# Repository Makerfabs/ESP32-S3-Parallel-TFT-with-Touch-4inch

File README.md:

# Makerfabs ESP32-S3 Parallel TFT with Touch 4inch

```c++
/*
Version:        V1.1
Author:            Vincent
Create Date:    2023/2/4
Note:
        V1.2：Now support LovyanGFX！
        V1.1: Add example and update readme.
*/
```

[TOC]

# Makerfabs

[Makerfabs home page](https://www.makerfabs.com/)

[Makerfabs Wiki](https://wiki.makerfabs.com/)

# Makerfabs ESP32-S3 Parallel TFT with Touch 4inch

## Intruduce

Product Link ：[ESP32-S3 Parallel TFT with Touch 4.0" 480*480 ST7701](https://www.makerfabs.com/esp32-s3-parallel-tft-with-touch-4-inch.html)

Wiki Link : [ESP32-S3 Parallel 4.0" TFT with Touch](https://wiki.makerfabs.com/ESP32_S3_Parallel_4.0_TFT_with_Touch.html)

The Latest ESP32-S3 4.0 inch display with 480*480 resolution, it integrated display/ touch/ audio speaker/ Lipo charger, to make this product ideal for applications such as IoT controlling, electronic photo frame, etc.

## Feature

- 4 inch RGB IPS display, it communicates with the controller ESP32S3 with 3SPI+RGB5/6/5 interface, with FPS >80;
- 5 points Touch;
- Onboard 16G SD card for storage;
- Lipo battery socket and charger, support any 3.7v lipo battery;
- On board speaker connector. This product is shipped with a 3 ohm 4w, 3528 speaker, the voice loud and clean, suitable for most applications;
- 2x Onboard Mabee connectors, support multiple Mabee/ Grove modules;

# Code

## Complier Option

- Install board : ESP32 .
- Install libraries：

[ESP32-audioI2S]([GitHub - schreibfaul1/ESP32-audioI2S: Play mp3 files from SD via I2S](https://github.com/schreibfaul1/ESP32-audioI2S))

- Use type-c use cable connect USB-TTL to PC.
- Select "ESP32-S3 DEV Module"
- Select PSRAM "OPI PSRAM"

"mf_Lvgl" library is modified from Lvgl library (version 8.3.2). 

Please unzip "lib/mf_Lvgl.zip" and copy to arduino library directory.

## Factory test program

\example\esp32s3_4.0_tft_fw_test

You can run this file test if you feel that your hardware is not working properly. 

In addition, it is necessary to decompress the compressed package in the sd_file folder and copy all the pictures and music in it to the TF card.

## Attention

Our Arduino_GFX_library version is 1.3.1, while the latest version is 1.3.4. The two versions are incompatible the running code. Our customer@Tim successfully ran the Arduino_gfx_Library version after modifying the configuration in the code on version 1.3.4.

```
Arduino_DataBus *bus = new Arduino_SWSPI(
    GFX_NOT_DEFINED /* DC */, 1 /* CS */,
    12 /* SCK */, 11 /* MOSI */, GFX_NOT_DEFINED /* MISO */);

Arduino_ESP32RGBPanel *rgbpanel = new Arduino_ESP32RGBPanel(
    45 /* DE */, 4 /* VSYNC */, 5 /* HSYNC */, 21 /* PCLK */,
    39 /* R0 */, 40 /* R1 */, 41 /* R2 */, 42 /* R3 */, 2 /* R4 */,
    0 /* G0 */, 9 /* G1 */, 14 /* G2 */, 47 /* G3 */, 48 /* G4 */, 3 /* G5 */,
    6 /* B0 */, 7 /* B1 */, 15 /* B2 */, 16 /* B3 */, 8 /* B4 */,
    1 /* hsync_polarity */, 10 /* hsync_front_porch */, 8 /* hsync_pulse_width */, 50 /* hsync_back_porch */,
    1 /* vsync_polarity */, 10 /* vsync_front_porch */, 8 /* vsync_pulse_width */, 20 /* vsync_back_porch */);

Arduino_RGB_Display *gfx = new Arduino_RGB_Display(
    480 /* width */, 480 /* height */, rgbpanel, 0 /* rotation */, true /* auto_flush */,
    bus, GFX_NOT_DEFINED /* RST */, st7701_type1_init_operations, sizeof(st7701_type1_init_operations));
```

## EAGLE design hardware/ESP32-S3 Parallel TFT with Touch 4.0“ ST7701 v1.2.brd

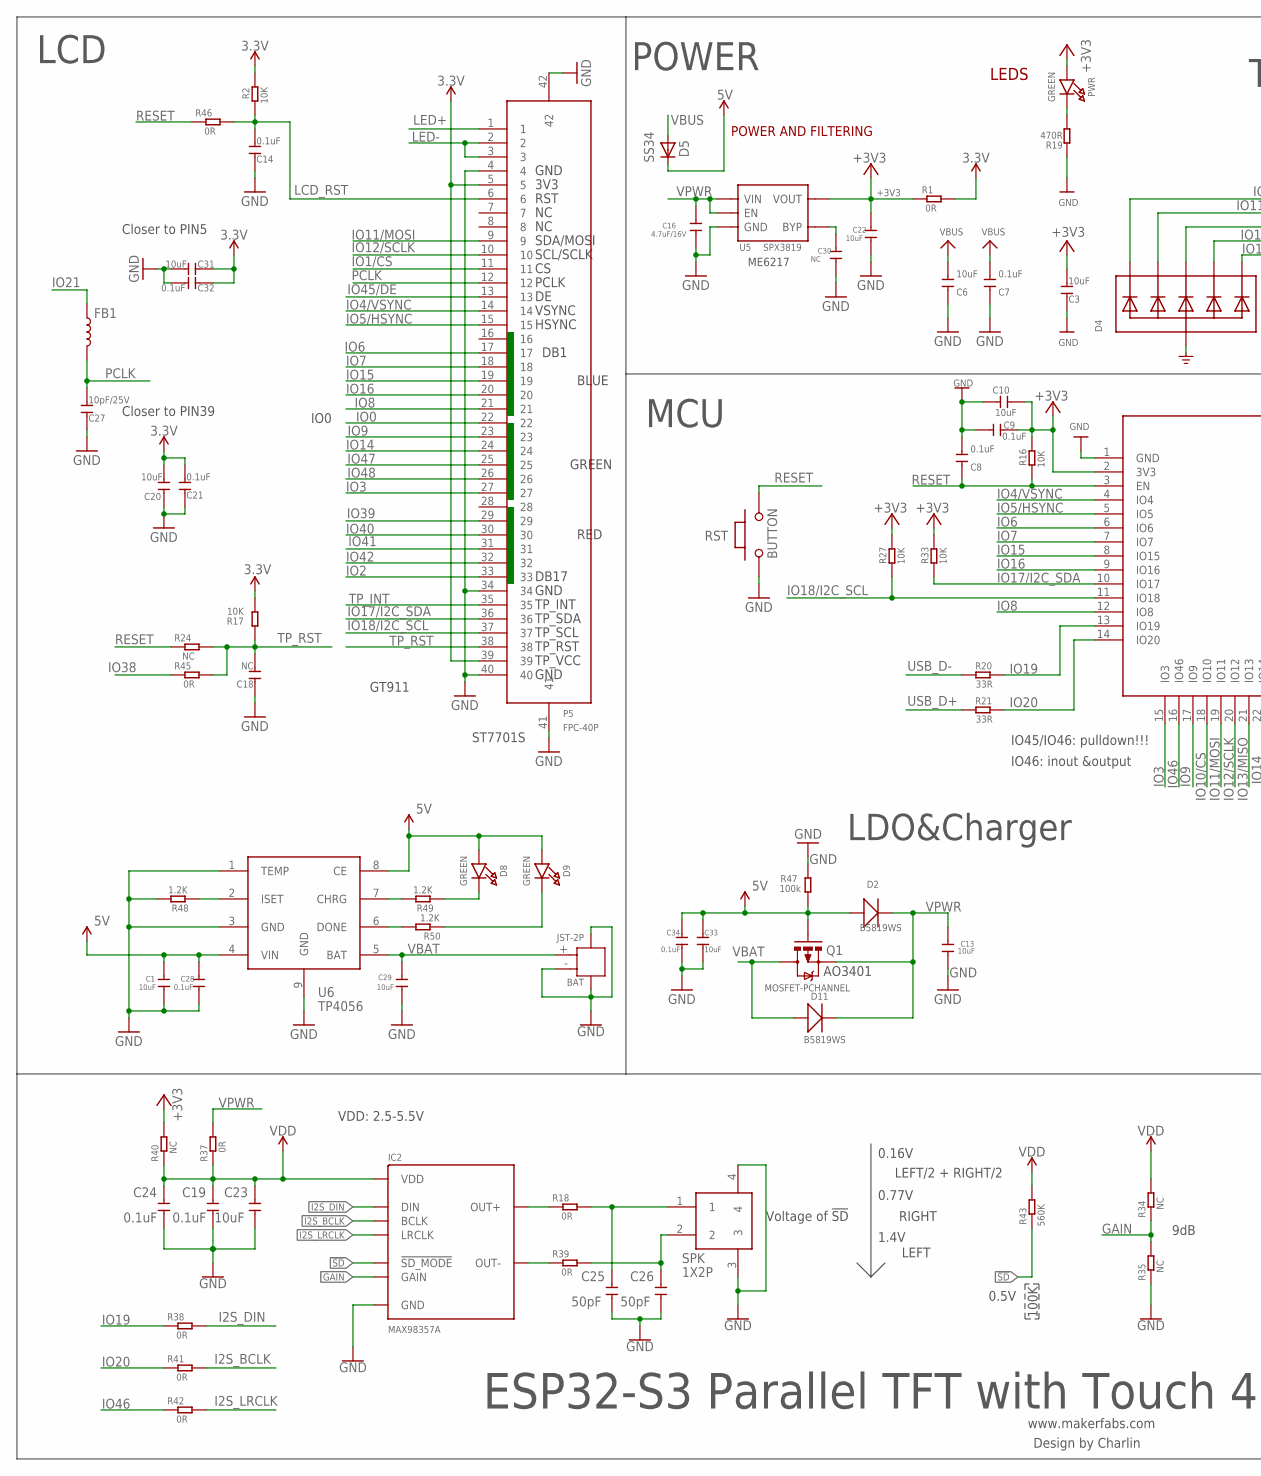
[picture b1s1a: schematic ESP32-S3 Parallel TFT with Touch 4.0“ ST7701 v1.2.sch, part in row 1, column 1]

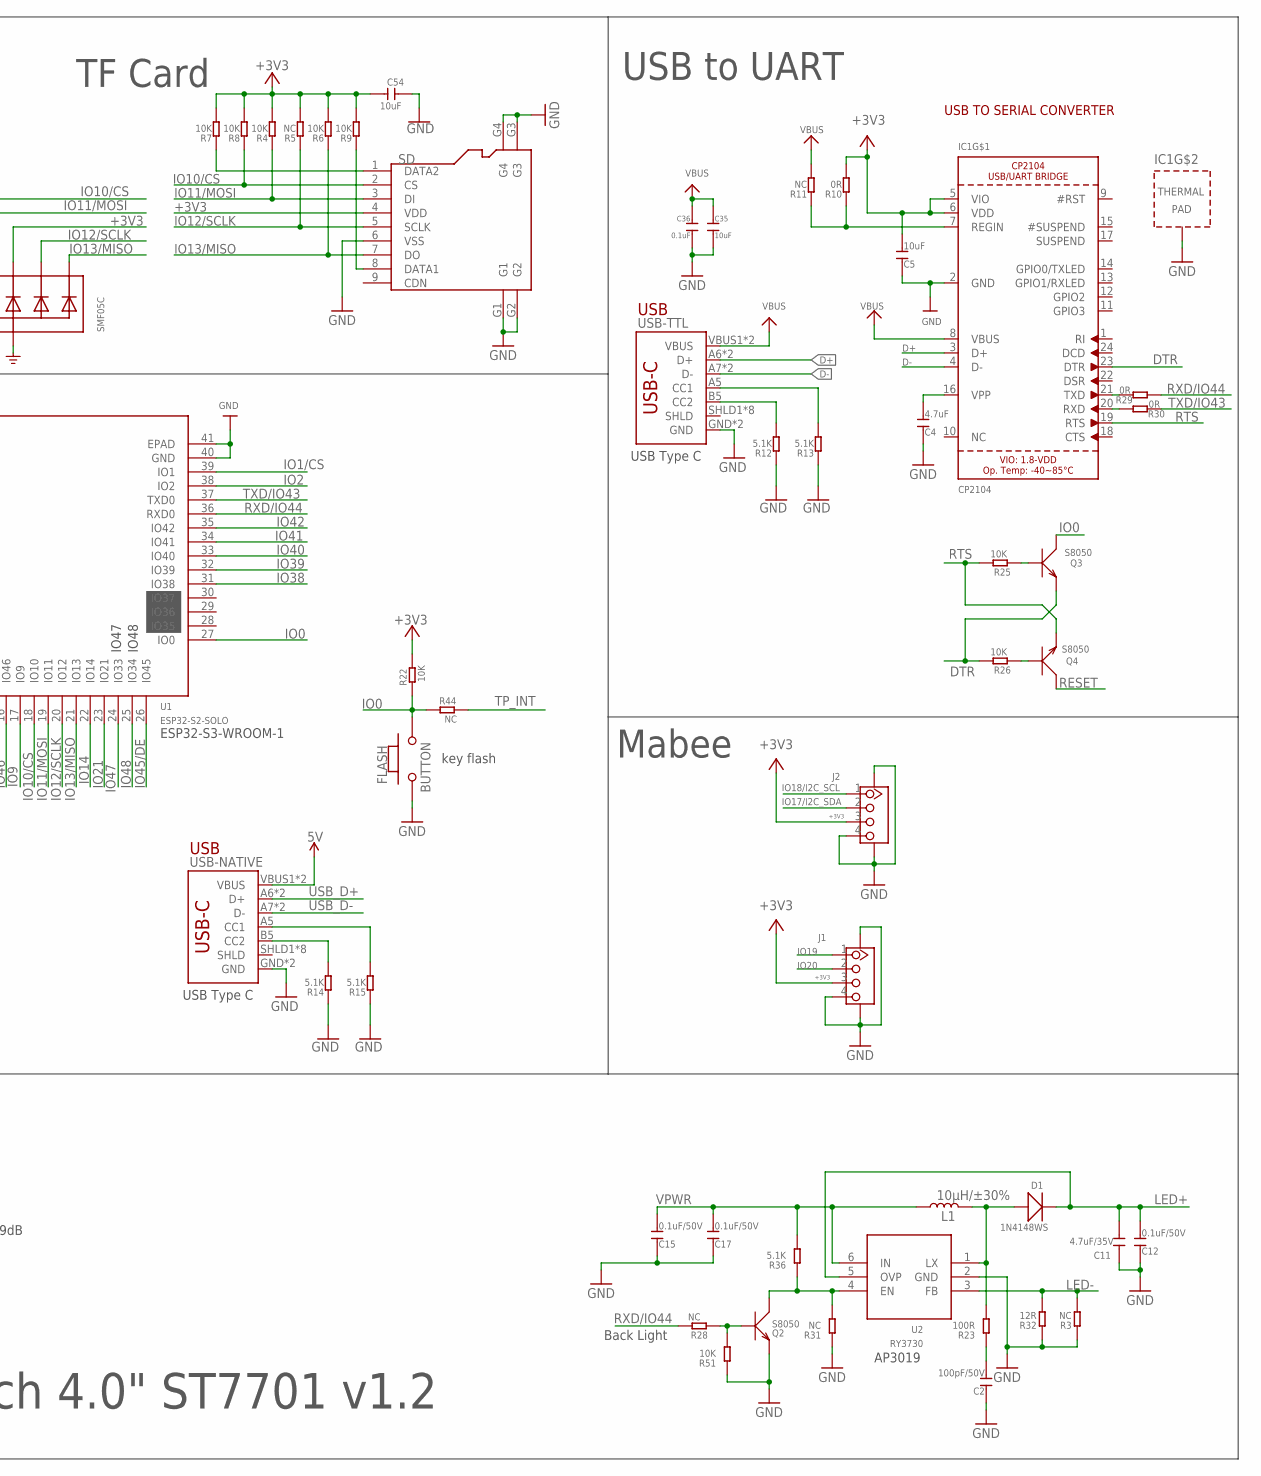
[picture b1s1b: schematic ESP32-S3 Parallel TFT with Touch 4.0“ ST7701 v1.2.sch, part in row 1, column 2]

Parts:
BAT: JST-2P; HW2-SMD-2.0-90D
C1, C13, C22, C23, C29, C33, C35: 10uF; 0603
C2: 100pF/50V; DISCRETE_C0603
C3, C5, C6, C10, C20, C31, C54: 10uF; DISCRETE_C0603
C4: 4.7uF; DISCRETE_C0603
C7, C8, C9, C14, C21, C32: 0.1uF; DISCRETE_C0603
C11: 4.7uF/35V; DISCRETE_C1206
C12, C15, C17: 0.1uF/50V; DISCRETE_C0603
C16: 4.7uF/16V; 0603
C18: NC; DISCRETE_C0603
C19, C24, C28, C34, C36: 0.1uF; 0603
C25, C26: 50pF; 0603
C27: 10pF/25V; DISCRETE_C0603
C30: NC; 0603
D1: 1N4148WS; SOD323
D2, D11: B5819WS; SOD323
D4: SMF05C; SOT363
D5: SS34; DO-214AC
D8, D9: GREEN; CHIPLED_0805_NOOUTLINE
FB1: INDUCTORFB-30OHM; 0603
FLASH: BUTTON; 157SW
IC1: CP2104; QFN24_4MM_SMSC
IC2: MAX98357A; TQFN-16
J1, J2: GROVE-CONNECTOR-SMD'90D'; HW4-SMD-2.0-90D
L1: 10µH/±30%; CR54
P5: FPC-40P; SMD42-50P-2560L490W
PWR: GREEN; CHIPLED_0805_NOOUTLINE
Q1: MOSFET-PCHANNEL; SOT23-3
Q2, Q3, Q4: S8050; SOT23
R1, R18, R29, R30, R37, R38, R39, R41, R42, R45, R46: 0R; R0603
R2, R16, R22, R25, R26, R27, R33: 10K; R0603
R3, R5, R11, R28, R31: NC; DISCRETE_R0603
R4, R6, R7, R8, R9, R17, R51: 10K; DISCRETE_R0603
R10: 0R; DISCRETE_R0603
R12, R13, R14, R15, R36: 5.1K; DISCRETE_R0603
R19: 470R; DISCRETE_R0603
R20, R21: 33R; R0603
R23: 100R; DISCRETE_R0603
R24, R34, R35, R40, R44: NC; R0603
R32: 12R; DISCRETE_R0603
R43: 560K; R0603
R47: 100k; R0603
R48, R49, R50: 1.2K; R0603
RST: BUTTON; 157SW
SD: HOLDER-MICROSD-9P; 9P-SMD-W/-RING
SPK: 1X2P; 1X2P-SMT1.25MM
U1: ESP32­S2­SOLO; ESP32-­S2-­SOLO
U2: RY3730; SOT23-6
U5: SPX3819; SOT23-5
U6: TP4056; SOP8-1.27P
USB-NATIVE: USB_C5; USB-C-16P-5
USB-TTL: USB_C5; USB-C-16P-5

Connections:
3.3V: C20.2, C21.2, C31.1, C32.1, P5.5, P5.39, R1.2, R2.2, R17.2
5V: C1.1, C28.1, C33.2, C34.1, D2.+, D5.C, D8.A, D9.A, Q1.1 (G), R47.1, U6.4 (VIN), U6.8 (CE), USB-NATIVE.VBUS1 (VBUS), USB-NATIVE.VBUS2 (VBUS)
!SD: IC2.P$4 (!SD_MODE), R43.1
+3V3: C3.2, C5.2, C9.1, C10.1, C22.1, C54.2, D4.4 (C3), IC1.5 (VIO), IC1.6 (VDD), J1.3, J2.3, PWR.A, R1.1, R4.2, R5.2, R6.2, R7.2, R8.2, R9.2, R10.2, R16.2, R22.2, R27.2, R33.2, R40.2, SD.4 (VDD), U1.2 (3V3), U5.5 (VOUT)
D+: IC1.3 (D+), USB-TTL.A6 (D+), USB-TTL.B6 (D+)
D-: IC1.4 (D-), USB-TTL.A7 (D-), USB-TTL.B7 (D-)
DTR: IC1.23 (DTR), Q3.2 (E), R26.2
GAIN: IC2.P$2 (GAIN), R34.1, R35.2
GND: BAT.3, BAT.4, BAT.- (2), C1.2, C2.1, C3.1, C4.1, C5.1, C6.1, C7.1, C8.2, C9.2, C10.2, C11.1, C12.1, C13.1, C14.1, C15.1, C16.2, C17.1, C18.1, C19.1, C20.1, C21.1, C22.2, C23.1, C24.1, C25.1, C26.1, C27.1, C28.2, C29.2, C30.2, C31.2, C32.2, C33.1, C34.2, C35.1, C36.2, C54.1, D4.2 (A), FLASH.1, IC1.2 (GND), IC1.THERM (TP), IC2.P$3 (GND), IC2.P$11 (GND), IC2.P$15 (GND), IC2.P$EP (GND), J1.4, J1.SS1, J1.SS2, J2.4, J2.SS1, J2.SS2, P5.4, P5.34, P5.40, P5.41, P5.42, Q2.2 (E), R3.1, R12.1, R13.1, R14.1, R15.1, R19.1, R31.1, R32.1, R35.1, R47.2, R48.2, R51.1, RST.1, SD.6 (VSS), SD.G1, SD.G2, SD.G3, SD.G4, SPK.3, SPK.4, U1.1 (GND), U1.40 (GND), U1.41 (EPAD), U2.2 (GND), U5.2 (GND), U6.1 (TEMP), U6.3 (GND), U6.9 (GND), USB-NATIVE.GND, USB-NATIVE.GND2 (GND), USB-TTL.GND, USB-TTL.GND2 (GND)
I2S_BCLK: IC2.P$16 (BCLK), R41.2
I2S_DIN: IC2.P$1 (DIN), R38.2
I2S_LRCLK: IC2.P$14 (LRCLK), R42.2
IO0: FLASH.2, P5.22, Q3.3 (C), R22.1, R44.1, U1.27 (IO0)
IO1/CS: P5.11, U1.39 (IO1)
IO2: P5.33, U1.38 (IO2)
IO3: P5.27, U1.15 (IO3)
IO4/VSYNC: P5.14, U1.4 (IO4)
IO5/HSYNC: P5.15, U1.5 (IO5)
IO6: P5.17, U1.6 (IO6)
IO7: P5.18, U1.7 (IO7)
IO8: P5.21, U1.12 (IO8)
IO9: P5.23, U1.17 (IO9)
IO10/CS: D4.1 (C1), R8.1, SD.2 (CS), U1.18 (IO10)
IO11/MOSI: D4.3 (C2), P5.9, R4.1, SD.3 (DI), U1.19 (IO11)
IO12/SCLK: D4.5 (C4), P5.10, R5.1, SD.5 (SCLK), U1.20 (IO12)
IO13/MISO: D4.6 (C5), R6.1, SD.7 (DO), U1.21 (IO13)
IO14: P5.24, U1.22 (IO14)
IO15: P5.19, U1.8 (IO15)
IO16: P5.20, U1.9 (IO16)
IO17/I2C_SDA: J2.2, P5.36, R33.1, U1.10 (IO17)
IO18/I2C_SCL: J2.1, P5.37, R27.1, U1.11 (IO18)
IO19: J1.1, R20.2, R38.1, U1.13 (IO19)
IO20: J1.2, R21.2, R41.1, U1.14 (IO20)
IO21: FB1.1, U1.23 (IO21)
IO38: R45.1, U1.31 (IO38)
IO39: P5.29, U1.32 (IO39)
IO40: P5.30, U1.33 (IO40)
IO41: P5.31, U1.34 (IO41)
IO42: P5.32, U1.35 (IO42)
IO45/DE: P5.13, U1.26 (IO45)
IO46: R42.1, U1.16 (IO46)
IO47: P5.25, U1.24 (IO33)
IO48: P5.26, U1.25 (IO34)
LCD_RST: C14.2, P5.6, R2.1, R46.2
LED+: C11.2, C12.2, D1.-, P5.1, U2.5 (OVP)
LED-: P5.2, P5.3, R3.2, R32.2, U2.3 (FB)
unnamed: C4.2, IC1.16 (VPP)
unnamed: Q4.1 (B), R26.1
unnamed: Q3.1 (B), R25.1
unnamed: IC2.P$9 (OUT+), R18.1
unnamed: R15.2, USB-NATIVE.A5 (CC1)
unnamed: PWR.C, R19.2
unnamed: Q2.1 (B), R28.1, R51.2
unnamed: R13.2, USB-TTL.A5 (CC1)
unnamed: R12.2, USB-TTL.B5 (CC2)
unnamed: IC1.7 (REGIN), R10.1, R11.1
unnamed: IC2.P$10 (OUT-), R39.1
unnamed: R14.2, USB-NATIVE.B5 (CC2)
unnamed: C25.2, R18.2, SPK.1
unnamed: C26.2, R39.2, SPK.2
unnamed: D1.+, L1.P$2 (2), R23.2, U2.1 (LX)
unnamed: IC1.21 (TXD), R29.2
unnamed: IC1.20 (RXD), R30.2
unnamed: C2.2, R23.1
unnamed: R48.1, U6.2 (ISET)
unnamed: Q2.3 (C), R31.2, R36.1, U2.4 (EN)
unnamed: R49.2, U6.7 (CHRG)
unnamed: R50.2, U6.6 (DONE)
unnamed: D8.C, R49.1
unnamed: D9.C, R50.1
unnamed: R7.1, SD.1 (DATA2)
unnamed: R9.1, SD.8 (DATA1)
unnamed: C30.1, U5.4 (BYP)
PCLK: C27.2, FB1.2, P5.12
RESET: C8.1, Q4.3 (C), R16.1, R24.1, R46.1, RST.2, U1.3 (EN)
RTS: IC1.19 (RTS), Q4.2 (E), R25.2
RXD/IO44: R28.2, R29.1, U1.36 (RXD0)
TP_INT: P5.35, R44.2
TP_RST: C18.2, P5.38, R17.1, R24.2, R45.2
TXD/IO43: R30.1, U1.37 (TXD0)
USB_D+: R21.1, USB-NATIVE.A6 (D+), USB-NATIVE.B6 (D+)
USB_D-: R20.1, USB-NATIVE.A7 (D-), USB-NATIVE.B7 (D-)
VBAT: BAT.+ (1), C29.1, D11.+, Q1.3 (D), U6.5 (BAT)
VBUS: C6.2, C7.2, C35.2, C36.1, D5.A, IC1.8 (VBUS), R11.2, USB-TTL.VBUS1 (VBUS), USB-TTL.VBUS2 (VBUS)
VDD: C19.2, C23.2, C24.2, IC2.P$7 (VDD), IC2.P$8 (VDD), R34.2, R37.1, R40.1, R43.2
VPWR: C13.2, C15.2, C16.1, C17.2, D2.-, D11.-, L1.P$1 (1), Q1.2 (S), R36.2, R37.2, U2.6 (IN), U5.1 (VIN), U5.3 (EN)

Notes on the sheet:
www.makerfabs.com
Design by Charlin
USB
LEDS
POWER AND FILTERING
USB TO SERIAL CONVERTER
key flash
ESP32-S3 Parallel TFT with Touch 4.0" ST7701 v1.2
POWER
USB to UART
USB Type C
TF Card
GT911
Back Light
IO45/IO46: pulldown!!!
IO46: inout &output
Mabee
LCD
MCU
ESP32-S3-WROOM-1
IO47
IO48
Closer to PIN5
3V3
DB1
RST
TP_INT
SDA/MOSI
SCL/SCLK
PCLK
VSYNC
HSYNC
TP_SDA
TP_SCL
TP_RST
TP_VCC
ST7701S
GND
DB17
BLUE

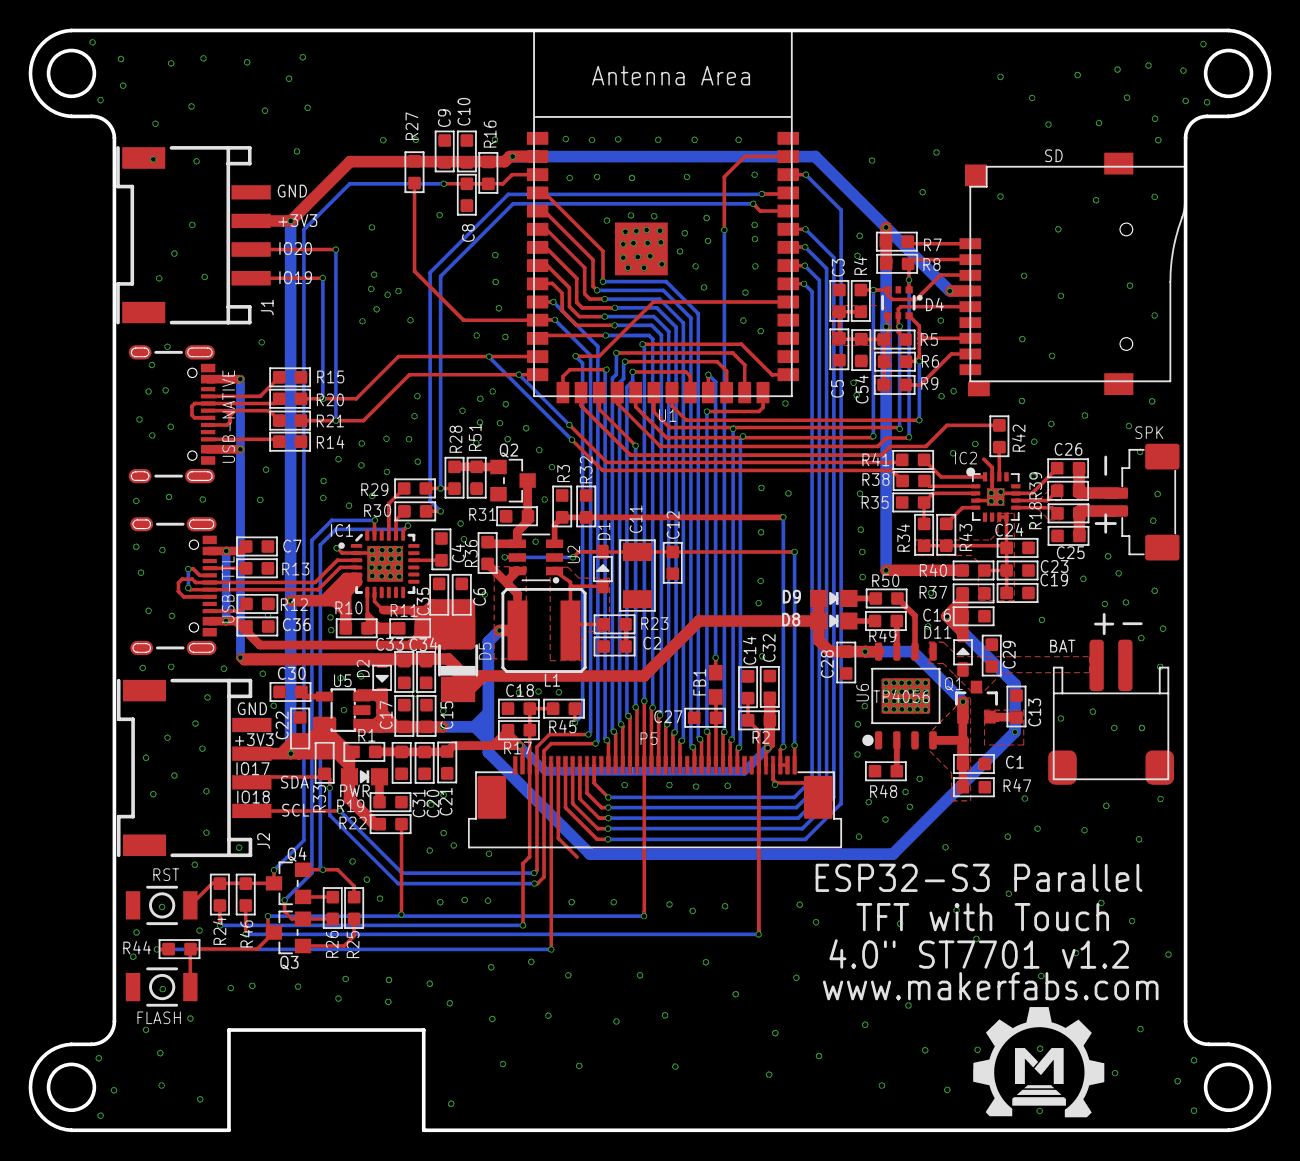
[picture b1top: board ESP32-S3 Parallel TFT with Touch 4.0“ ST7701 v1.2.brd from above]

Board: 2 copper layers, 86.5 x 76.8 mm, 119 parts (0 on the bottom side), 86 nets.

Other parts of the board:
U$1: MAKERFABS_0.3

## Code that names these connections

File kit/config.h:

#ifndef MF_CONFIG_H
#define MF_CONFIG_H

#include <SPI.h>
#include <FS.h>
#include <Wire.h>
#include <SD.h>
#include <Audio.h>
#include <Arduino_GFX_Library.h>
#include <TAMC_GT911.h>
#include <ArduinoJson.h>
#include <HTTPClient.h>
#include <Adafruit_MLX90640.h>
#include <Adafruit_SGP30.h>
#include <Adafruit_SHT31.h>
#include <ESPAsyncWebServer.h>

#include "JpegFunc.h"

// SD
#define SD_SCK 12
#define SD_MISO 13
#define SD_MOSI 11
#define SD_CS 10

// I2S
#define I2S_DOUT 19
#define I2S_BCLK 20
#define I2S_LRCK 46

// Touch
#define I2C_SDA_PIN 17
#define I2C_SCL_PIN 18
#define TOUCH_INT -1
#define TOUCH_RST 38

#define TOUCH_ROTATION ROTATION_NORMAL
#define TOUCH_MAP_X1 480
#define TOUCH_MAP_X2 0
#define TOUCH_MAP_Y1 480
#define TOUCH_MAP_Y2 0

#define B_NUM_MAIN 4
#define B_COUNTY_NUM 8

#define SSID "Makerfabs"
#define PWD "20160704"

// MLX90640
#define MLX_I2C_ADDR 0x33

#endif

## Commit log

2023-02-04 Create object
2023-02-04 Add hardware
2023-02-07 Add example
2023-02-13 Edit readme
2023-02-24 Kit_demo
2023-03-01 Page2
2023-03-02 Add LovyanGFX demo
2023-03-03 Weather Function
2023-03-04 Time display
2023-03-06 Fix weather page
2023-03-07 Add schematic PDF file
2023-03-08 MLX90640
2023-03-08 Fix weather bug
2023-03-09 多线程bug修复
2023-03-09 Touch rst fix
2023-03-10 TVOC
2023-03-10 Fix music bug
2023-03-10 Change weather ui
2023-03-13 Repair MLX90640 bug
2023-03-13 Change UI
2023-03-14 Change TVOC UI
2023-03-14 调整文件夹结构
2023-03-14 Change file location
2023-03-14 Change country
2023-05-17 Change Weather API
2023-05-31 Add mpu6050 demo
2023-08-15 Add file system demo
2024-05-20 Adding @bitbank2 example to decode GIF as fast as possible
2024-05-20 Clenup AnimatedGIF example
2024-07-31 add demo

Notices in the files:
parts and their libraries:
microbuilder: This work is placed in the public domain, and may be freely used for commercial and non-commercial work with the following conditions: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
SparkFun-Coils: Licensing: Creative Commons ShareAlike 4.0 International - https://creativecommons.org/licenses/by-sa/4.0
